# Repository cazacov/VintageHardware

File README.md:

# Vintage Hardware

## Olivetti M24

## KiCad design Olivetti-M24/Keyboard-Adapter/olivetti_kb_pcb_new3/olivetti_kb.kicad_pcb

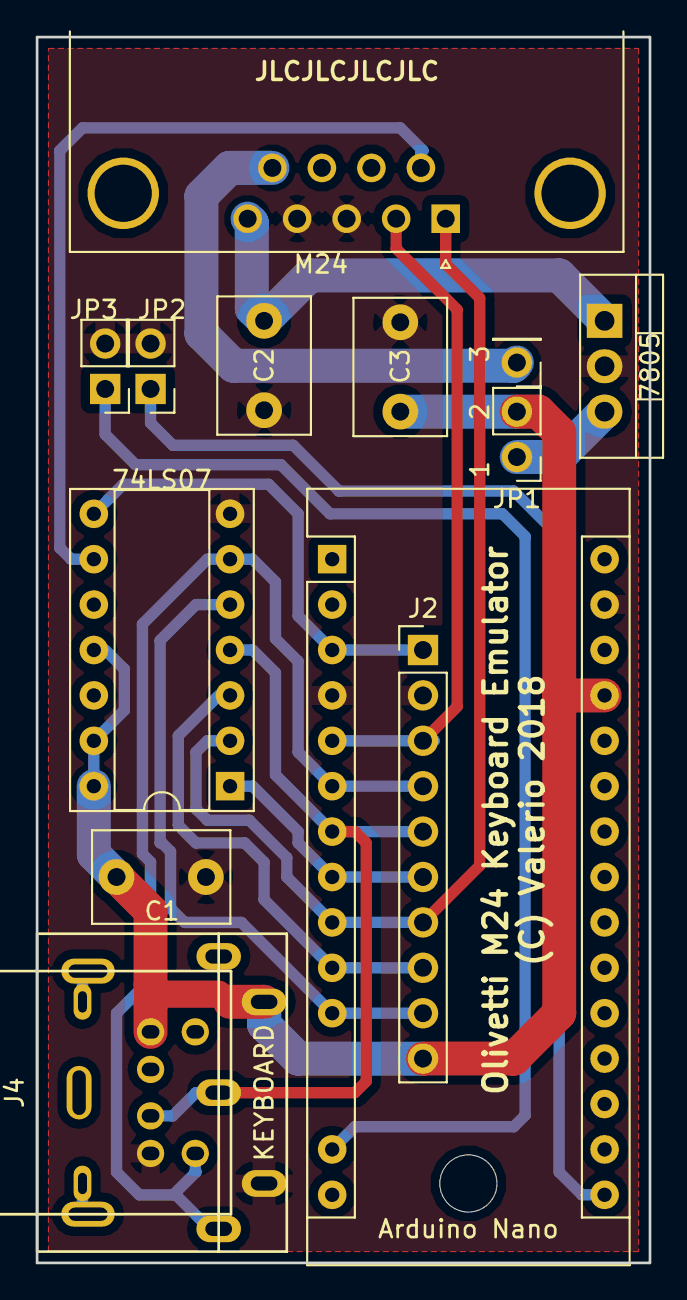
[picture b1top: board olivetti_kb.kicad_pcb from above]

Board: 2 copper layers, 34.3 x 68.6 mm, 14 parts (0 on the bottom side), 16 nets.

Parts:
1   2   3: 5V_M24; PinHeader_1x01_P2.54mm_Vertical
74LS07: 74LS07; DIP-14_W7.62mm_Socket
7805: LM7805_TO220; TO-220-3_Vertical
Arduino Nano: Arduino_Nano_v3.x; Arduino_Nano
C1, C3: 100n; C_Disc_D7.5mm_W5.0mm_P5.00mm
C2: 330n; C_Disc_D7.5mm_W5.0mm_P5.00mm
J2: Test; PinHeader_1x10_P2.54mm_Vertical
J4: Mini-DIN-6; Mini_DIN_6p
JP1: 5V_reg; PinHeader_1x02_P2.54mm_Vertical
JP2: DEBUG; PinHeader_1x02_P2.54mm_Vertical
JP3: TTY; PinHeader_1x02_P2.54mm_Vertical
KEYBOARD: DIN-5_180degree; DIN_5p_41524
M24: DB9_Male; DSUB-9_Male_Horizontal_P2.77x2.84mm_EdgePinOffset7.70mm_Hou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

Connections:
+5V: 74LS07.11, 74LS07.13, 74LS07.14, Arduino Nano.27, C1.1, C3.1, J2.10, J4.4, JP1.2, KEYBOARD.5
/+12V: 7805.1, C2.1, M24.5
/~M24_RESET: 74LS07.9, M24.6
AT_CLOCK: 74LS07.6, Arduino Nano.6, J2.4, J4.5, KEYBOARD.1
AT_CLOCK_WR: 74LS07.5, Arduino Nano.11, J2.9
AT_DATA: 74LS07.4, Arduino Nano.7, J2.5, J4.1, KEYBOARD.2
AT_DATA_WR: 74LS07.3, Arduino Nano.10, J2.8
GND: 74LS07.7, 7805.2, Arduino Nano.4, Arduino Nano.29, C1.2, C2.2, C3.2, J2.2, J4.3, JP2.2, JP3.2, KEYBOARD.4, M24.3, M24.4
M24_CLOCK: Arduino Nano.5, J2.3, M24.2
M24_DATA: 74LS07.2, Arduino Nano.9, J2.7, M24.1
M24_DATA_WR: 74LS07.1, Arduino Nano.8, J2.6
unnamed: Arduino Nano.14, JP3.1
unnamed: Arduino Nano.16, JP2.1
unnamed: 1 2 3.1, M24.9
unnamed: 7805.3, JP1.1
RESET: 74LS07.8, Arduino Nano.3, J2.1

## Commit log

2021-01-10 Add M24 keyboard emulation library
